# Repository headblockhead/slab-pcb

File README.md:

# Slab PCB

The full PCB, schematics, and gerber downloads for the [Slab keyboard project](https://github.com/headblockhead/slab).

Downloads are in the releases section.

## Layers

- The layer `User.3` stores non-polygon versions of the silkscreen text elements that can be edited.
- The layer `User.6` stores a printable outline of keyswitch locations, so a keymap can be drawn on paper to test the layout.

## Building

This project uses [Nix](https://nixos.org) for CI/CD only, to generate gerber files using KiCAD's CLI.

## Sponsorship

The PCB prototypes for this version of the Slab keyboard project were kindly provided by [PCBX](https://link.pcbx.com/fddd) for free!

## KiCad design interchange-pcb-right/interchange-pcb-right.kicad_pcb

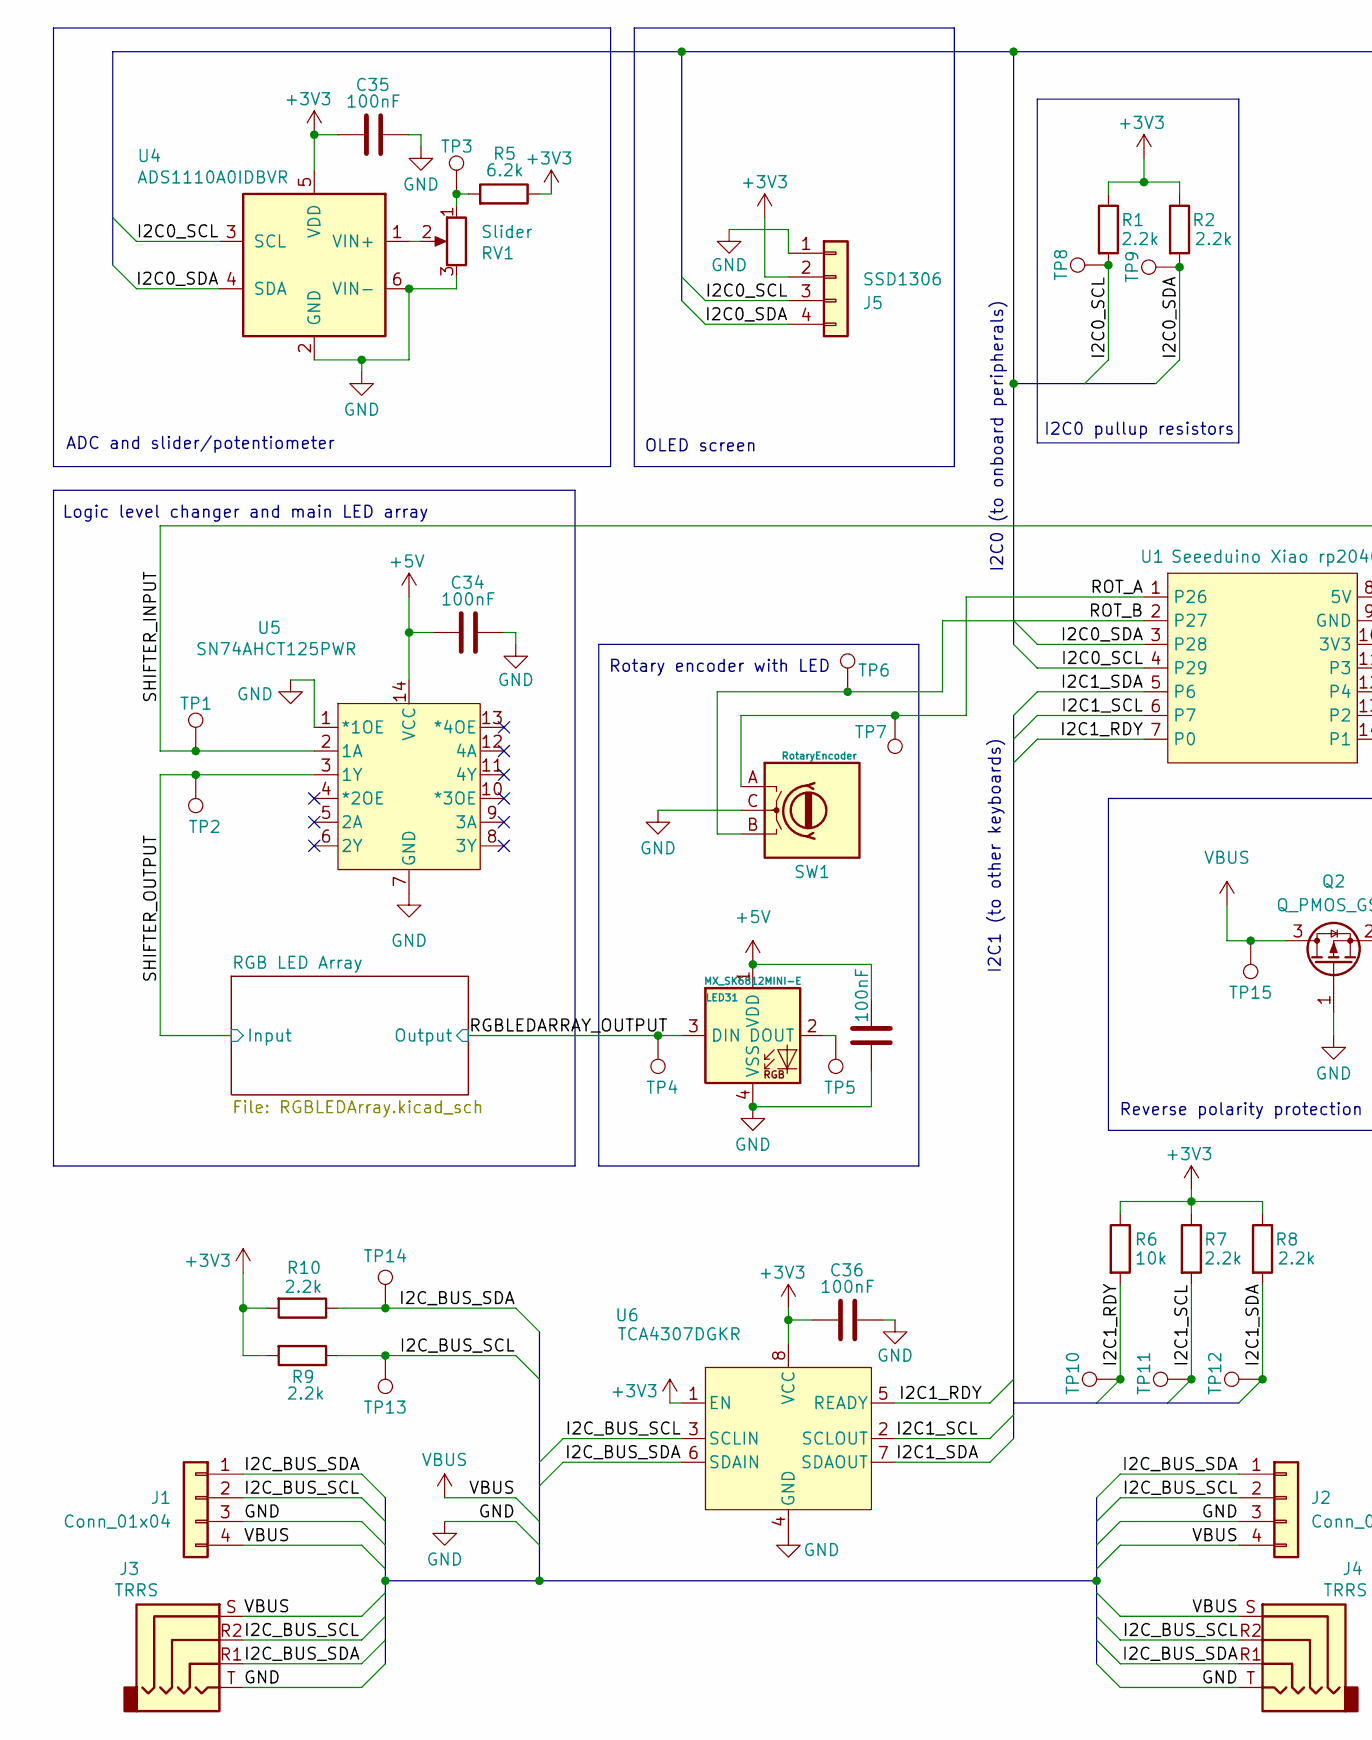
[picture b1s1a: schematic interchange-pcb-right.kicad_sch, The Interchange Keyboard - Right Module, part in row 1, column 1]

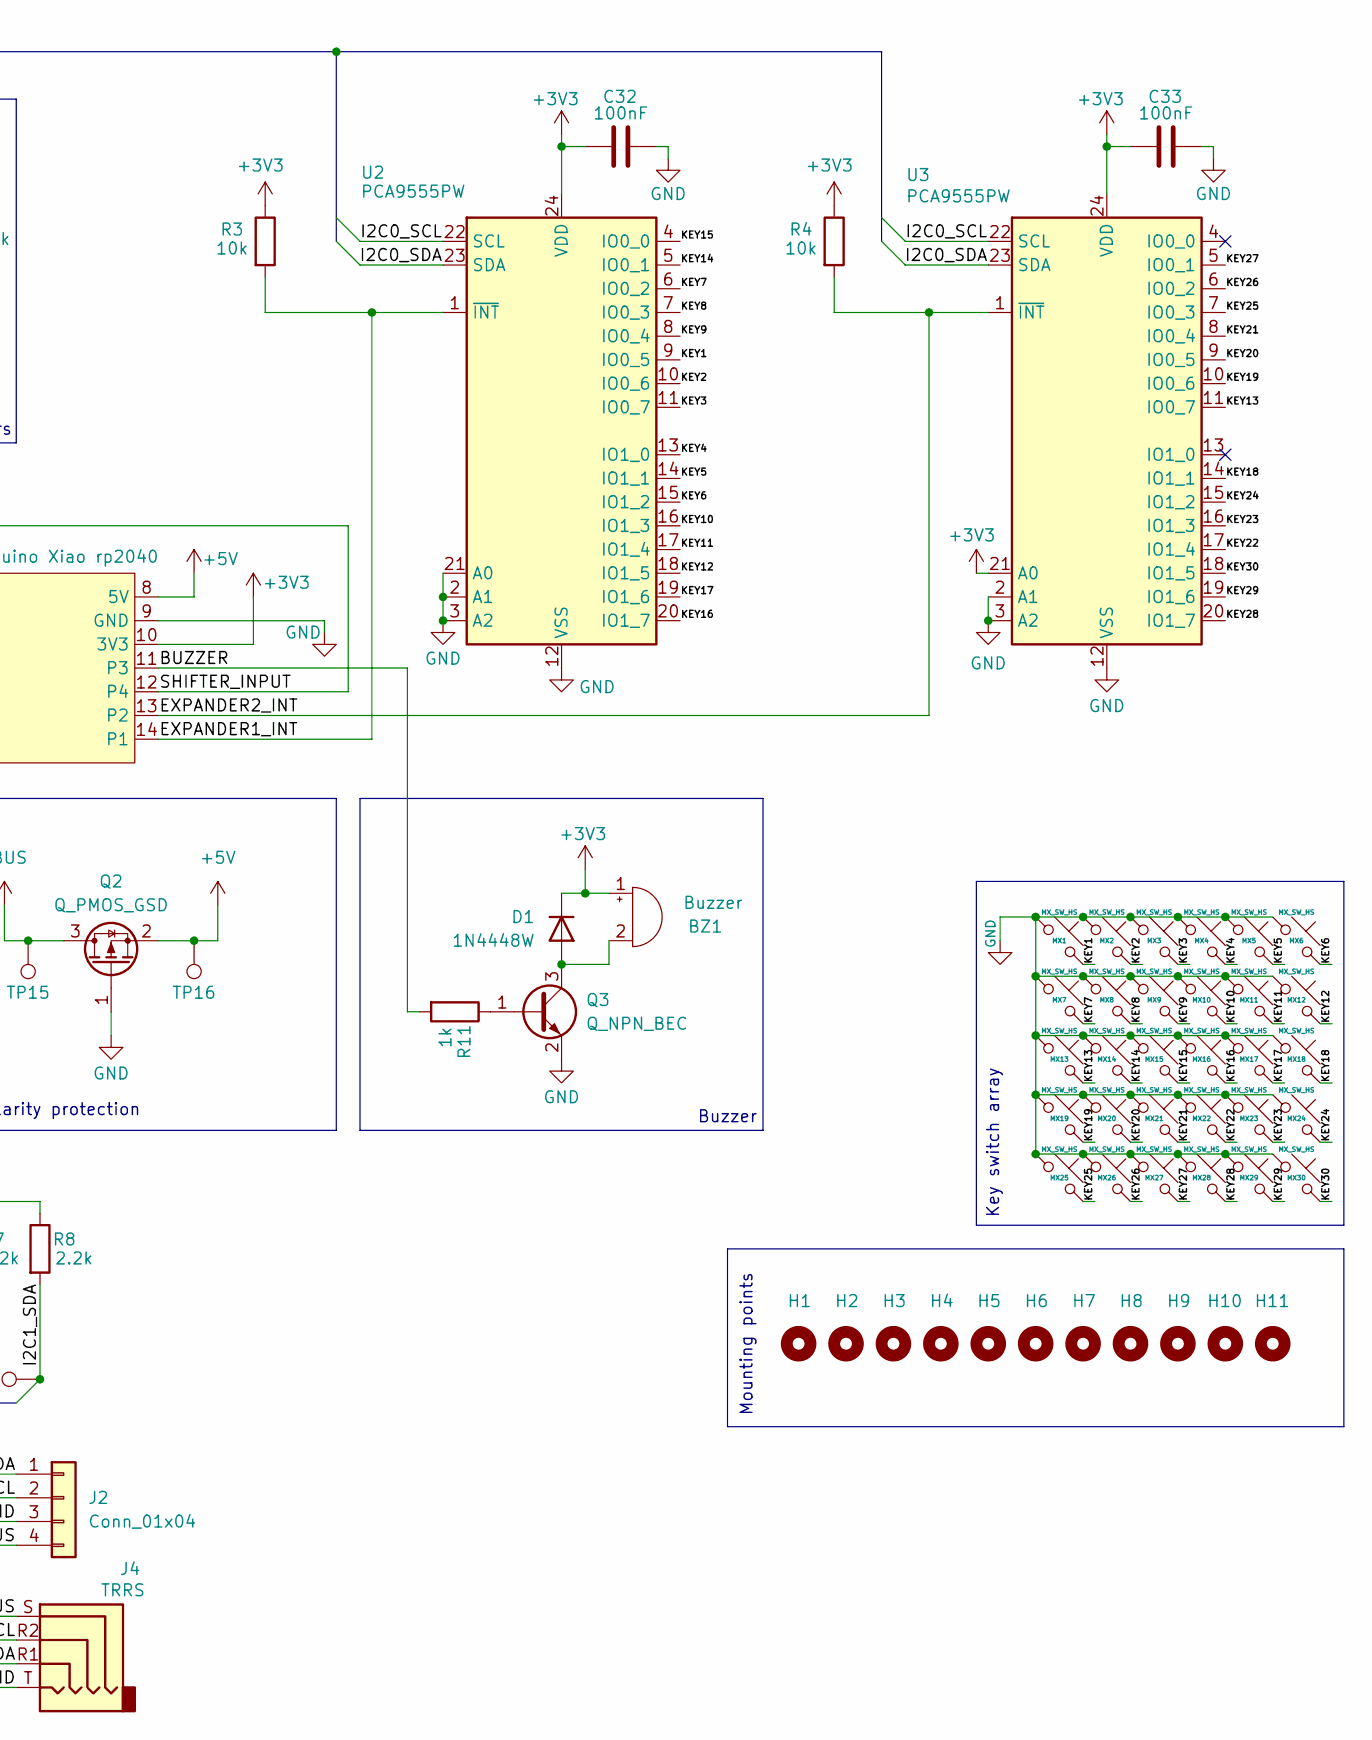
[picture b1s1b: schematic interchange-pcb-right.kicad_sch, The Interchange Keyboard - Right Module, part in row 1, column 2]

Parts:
BZ1: Buzzer; buzzer; LCSC C94599
C31, C32, C33, C34, C35, C36: 100nF; C_0603_1608Metric_Pad1.08x0.95mm_HandSolder; LCSC C14663
D1: 1N4448W; D_SOD-123; LCSC C5190208
H1, H2, H3, H4, H5, H6, H7, H8, H9, H10, H11: MountingHole_Pad; MountingHole_3.2mm_M3
J1: Conn_01x04; MagneticSlot_Right
J2: Conn_01x04; MagneticSlot_Left
J3, J4: TRRS; Jack_3.5mm_KoreanHropartsElec_PJ-320D-4A_Horizontal; LCSC C95562
J5: SSD1306; SSD1306_128x32; LCSC C5248081
LED31: MX_SK6812MINI-E; LED_6028R_Custom; LCSC C5149201
MX1, MX2, MX3, MX4, MX5, MX6, MX7, MX8, MX9, MX10, MX11, MX12, MX13, MX14, MX15, MX16, MX17, MX18, MX19, MX20, MX21, MX22, MX23, MX24, MX25, MX26, MX27, MX28, MX29, MX30: MX_SW_HS; SW_choc_mx_combined; LCSC C41430893
Q2: Q_PMOS_GSD; SOT-23_Handsoldering; LCSC C54157814
Q3: Q_NPN_BEC; SOT-23_Handsoldering; LCSC C57668
R1, R2, R7, R8, R9, R10: 2.2k; R_0603_1608Metric_Pad0.98x0.95mm_HandSolder; LCSC C4190
R3, R4, R6: 10k; R_0603_1608Metric_Pad0.98x0.95mm_HandSolder; LCSC C2930027
R5: 6.2k; R_0603_1608Metric_Pad0.98x0.95mm_HandSolder; LCSC C2907186
R11: 1k; R_0603_1608Metric_Pad0.98x0.95mm_HandSolder; LCSC C2907113
RV1: Slider; SW_RS45111A900F_ALPS; LCSC C470640
SW1: RotaryEncoder; RotaryEncoder_Alps_EC12E_Vertical_H20mm_Custom; LCSC C351235
TP1, TP2, TP3, TP4, TP5, TP6, TP7, TP8, TP9, TP10, TP11, TP12, TP13, TP14, TP15, TP16: TestPoint; TestPoint_Pad_D1.5mm
U1: Seeeduino Xiao rp2040; Xiao_rp2040_AC_Reflow_Custom
U2, U3: PCA9555PW; TSSOP-24_4.4x7.8mm_P0.65mm; LCSC C128392
U4: ADS1110A0IDBVR; SOT-23-6_Handsoldering; LCSC C16598
U5: SN74AHCT125PWR; LCSC C36365
U6: TCA4307DGKR; SOIC8_DGK_TEX; LCSC C880333

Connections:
+3V3: BZ1.1 (+), C32.2, C33.2, C35.2, C36.2, D1.1 (K), J5.2, R1.1, R2.1, R3.1, R4.1, R5.1, R6.1, R7.1, R8.1, R9.2, R10.2, U1.10 (3V3), U2.24 (VDD), U3.21 (A0), U3.24 (VDD), U4.5 (VDD), U6.1 (EN), U6.8 (VCC)
+5V: C31.2, C34.2, LED31.1 (VDD), Q2.2 (S), TP16.1 (1_1), U1.8 (5V), U5.14 (VCC); also elsewhere on the board
/BUZZER: R11.2, U1.11 (P3)
/EXPANDER1_INT: R3.2, U1.14 (P1), U2.1 (~INT)
/EXPANDER2_INT: R4.2, U1.13 (P2), U3.1 (~INT)
/I2C0_SCL: J5.3, R1.2, TP8.1 (1_1), U1.4 (P29), U2.22 (SCL), U3.22 (SCL), U4.3 (SCL)
/I2C0_SDA: J5.4, R2.2, TP9.1 (1_1), U1.3 (P28), U2.23 (SDA), U3.23 (SDA), U4.4 (SDA)
/I2C1_RDY: R6.2, TP10.1 (1_1), U1.7 (P0), U6.5 (READY)
/I2C1_SCL: R7.2, TP11.1 (1_1), U1.6 (P7), U6.2 (SCLOUT)
/I2C1_SDA: R8.2, TP12.1 (1_1), U1.5 (P6), U6.7 (SDAOUT)
/I2C_BUS_SCL: J1.2, J2.2, J3.R2, J4.R2, R9.1, TP13.1 (1_1), U6.3 (SCLIN)
/I2C_BUS_SDA: J1.1, J2.1, J3.R1, J4.R1, R10.1, TP14.1 (1_1), U6.6 (SDAIN)
/KEY1: MX1.2, U2.9 (IO0_5)
/KEY2: MX2.2, U2.10 (IO0_6)
/KEY3: MX3.2, U2.11 (IO0_7)
/KEY4: MX4.2, U2.13 (IO1_0)
/KEY5: MX5.2, U2.14 (IO1_1)
/KEY6: MX6.2, U2.15 (IO1_2)
/KEY7: MX7.2, U2.6 (IO0_2)
/KEY8: MX8.2, U2.7 (IO0_3)
/KEY9: MX9.2, U2.8 (IO0_4)
/KEY10: MX10.2, U2.16 (IO1_3)
/KEY11: MX11.2, U2.17 (IO1_4)
/KEY12: MX12.2, U2.18 (IO1_5)
/KEY13: MX13.2, U3.11 (IO0_7)
/KEY14: MX14.2, U2.5 (IO0_1)
/KEY15: MX15.2, U2.4 (IO0_0)
/KEY16: MX16.2, U2.20 (IO1_7)
/KEY17: MX17.2, U2.19 (IO1_6)
/KEY18: MX18.2, U3.14 (IO1_1)
/KEY19: MX19.2, U3.10 (IO0_6)
/KEY20: MX20.2, U3.9 (IO0_5)
/KEY21: MX21.2, U3.8 (IO0_4)
/KEY22: MX22.2, U3.17 (IO1_4)
/KEY23: MX23.2, U3.16 (IO1_3)
/KEY24: MX24.2, U3.15 (IO1_2)
/KEY25: MX25.2, U3.7 (IO0_3)
/KEY26: MX26.2, U3.6 (IO0_2)
/KEY27: MX27.2, U3.5 (IO0_1)
/KEY28: MX28.2, U3.20 (IO1_7)
/KEY29: MX29.2, U3.19 (IO1_6)
/KEY30: MX30.2, U3.18 (IO1_5)
/RGBLEDARRAY_OUTPUT: LED31.3 (DIN), TP4.1 (1_1); also elsewhere on the board
/ROT_A: SW1.A, TP7.1 (1_1), U1.1 (P26)
/ROT_B: SW1.B, TP6.1 (1_1), U1.2 (P27)
/SHIFTER_INPUT: TP1.1 (1_1), U1.12 (P4), U5.2 (1A)
/SHIFTER_OUTPUT: TP2.1 (1_1), U5.3 (1Y); also elsewhere on the board
GND: C31.1, C32.1, C33.1, C34.1, C35.1, C36.1, J1.3, J2.3, J3.T, J4.T, J5.1, LED31.4 (VSS), MX1.1, MX2.1, MX3.1, MX4.1, MX5.1, MX6.1, MX7.1, MX8.1, MX9.1, MX10.1, MX11.1, MX12.1, MX13.1, MX14.1, MX15.1, MX16.1, MX17.1, MX18.1, MX19.1, MX20.1, MX21.1, MX22.1, MX23.1, MX24.1, MX25.1, MX26.1, MX27.1, MX28.1, MX29.1, MX30.1, Q2.1 (G), Q3.2 (E), RV1.3, SW1.C, U1.9 (GND), U2.2 (A1), U2.3 (A2), U2.12 (VSS), U2.21 (A0), U3.2 (A1), U3.3 (A2), U3.12 (VSS), U4.2 (GND), U4.6 (VIN-), U5.1 (*1OE), U5.7 (GND), U6.4 (GND); also elsewhere on the board
unnamed: BZ1.2 (-), D1.2 (A), Q3.3 (C)
unnamed: LED31.2 (DOUT), TP5.1 (1_1)
unnamed: Q3.1 (B), R11.1
unnamed: R5.2, RV1.1, TP3.1 (1_1)
unnamed: RV1.2, U4.1 (VIN+)
VBUS: J1.4, J2.4, J3.S, J4.S, Q2.3 (D), TP15.1 (1_1)

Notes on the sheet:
I2C0 (to onboard peripherals)
I2C1 (to other keyboards)
Mounting points
OLED screen
Reverse polarity protection
Rotary encoder with LED
Buzzer
I2C0 pullup resistors
ADC and slider/potentiometer
Key switch array
Logic level changer and main LED array

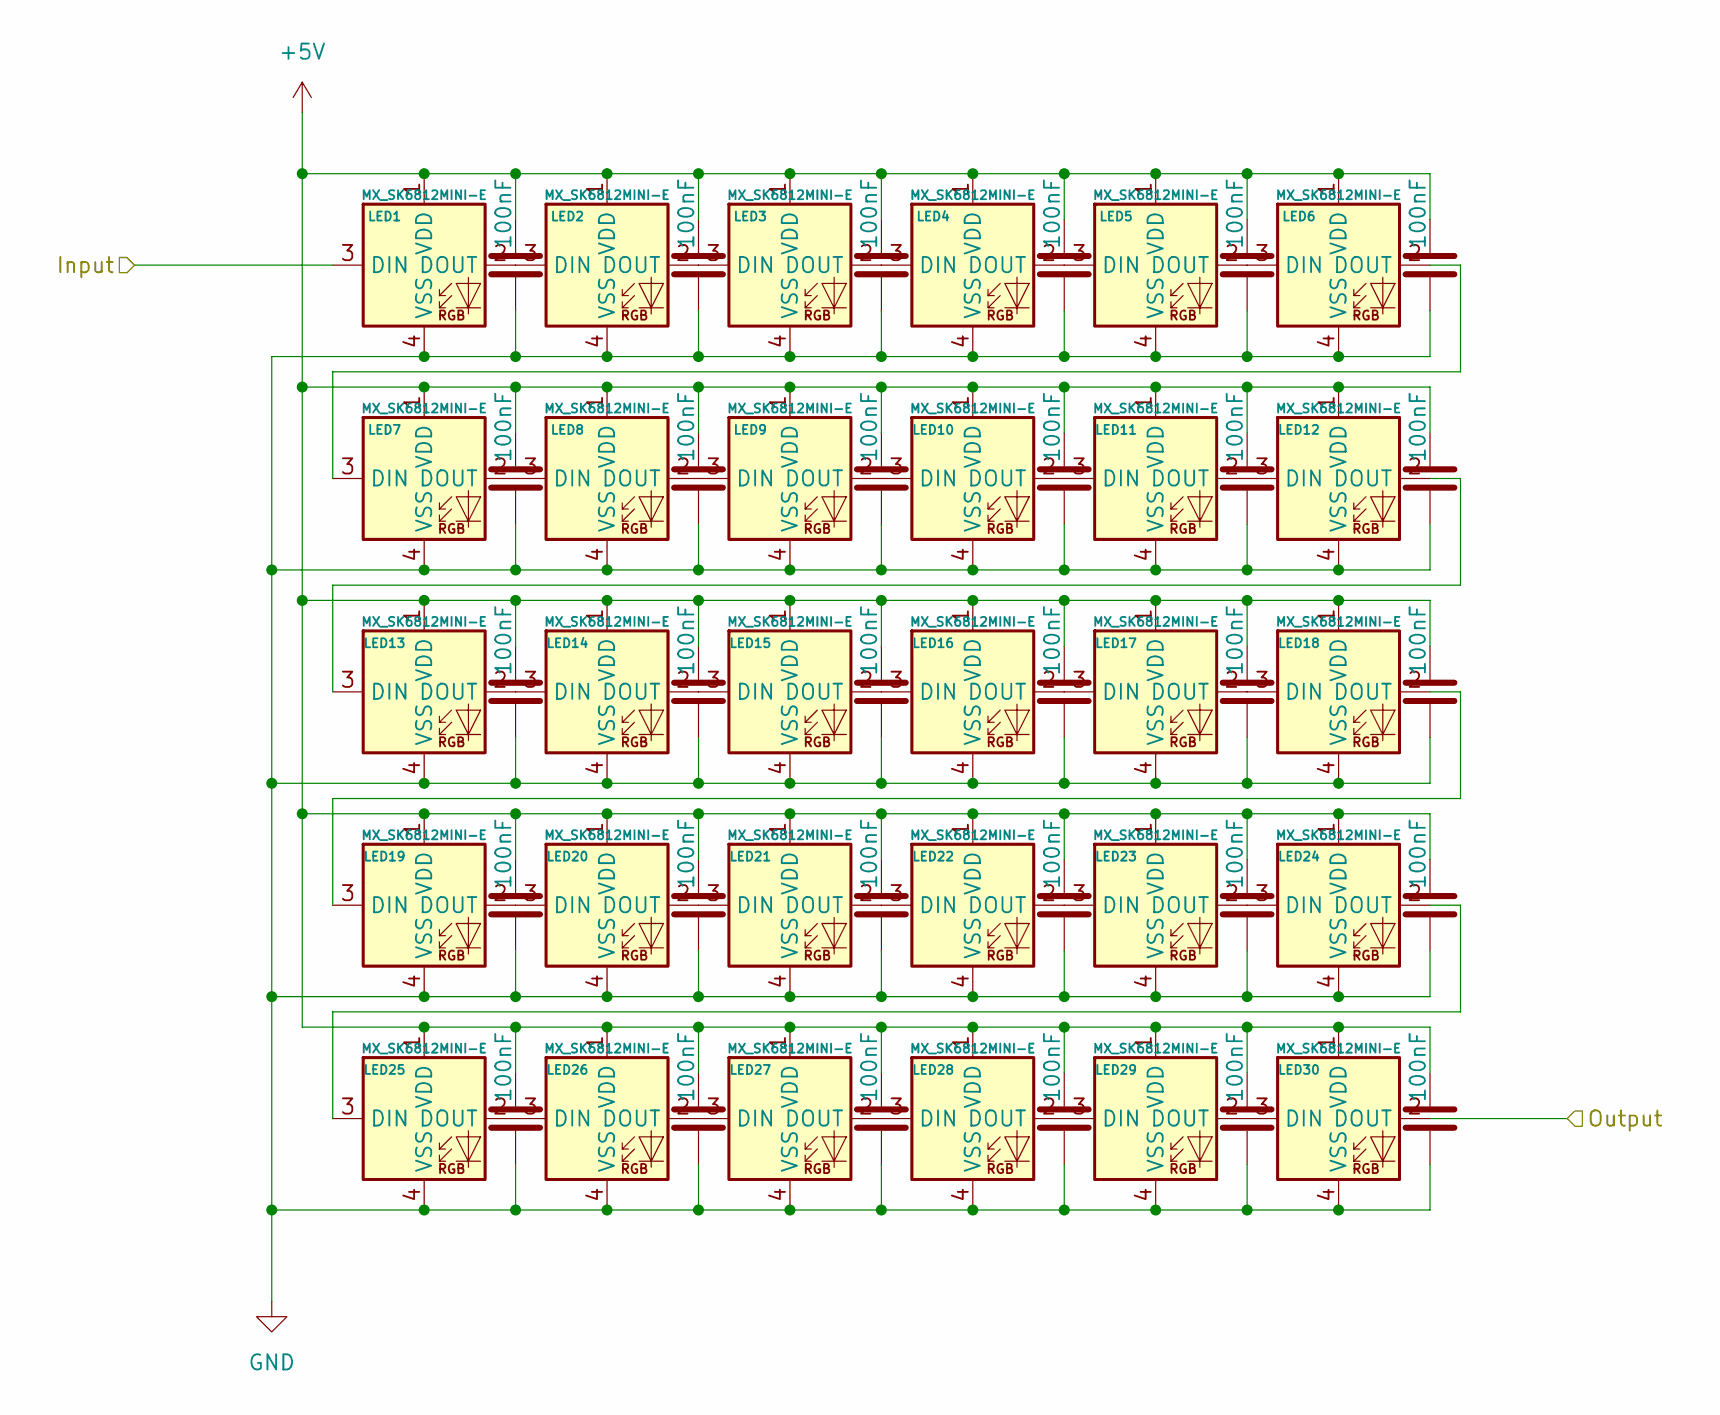
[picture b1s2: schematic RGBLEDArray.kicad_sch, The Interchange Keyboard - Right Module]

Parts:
C1, C2, C3, C4, C5, C6, C7, C8, C9, C10, C11, C12, C13, C14, C15, C16, C17, C18, C19, C20, C21, C22, C23, C24, C25, C26, C27, C28, C29, C30: 100nF; C_0603_1608Metric_Pad1.08x0.95mm_HandSolder; LCSC C14663
LED1, LED2, LED3, LED4, LED5, LED6, LED7, LED8, LED9, LED10, LED11, LED12, LED13, LED14, LED15, LED16, LED17, LED18, LED19, LED20, LED21, LED22, LED23, LED24, LED25, LED26, LED27, LED28, LED29, LED30: MX_SK6812MINI-E; LED_MX_6028R-ROT_Custom; LCSC C5149201

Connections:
+5V: C1.2, C2.2, C3.2, C4.2, C5.2, C6.2, C7.2, C8.2, C9.2, C10.2, C11.2, C12.2, C13.2, C14.2, C15.2, C16.2, C17.2, C18.2, C19.2, C20.2, C21.2, C22.2, C23.2, C24.2, C25.2, C26.2, C27.2, C28.2, C29.2, C30.2, LED1.1 (VDD), LED2.1 (VDD), LED3.1 (VDD), LED4.1 (VDD), LED5.1 (VDD), LED6.1 (VDD), LED7.1 (VDD), LED8.1 (VDD), LED9.1 (VDD), LED10.1 (VDD), LED11.1 (VDD), LED12.1 (VDD), LED13.1 (VDD), LED14.1 (VDD), LED15.1 (VDD), LED16.1 (VDD), LED17.1 (VDD), LED18.1 (VDD), LED19.1 (VDD), LED20.1 (VDD), LED21.1 (VDD), LED22.1 (VDD), LED23.1 (VDD), LED24.1 (VDD), LED25.1 (VDD), LED26.1 (VDD), LED27.1 (VDD), LED28.1 (VDD), LED29.1 (VDD), LED30.1 (VDD); also elsewhere on the board
/RGBLEDARRAY_OUTPUT: LED30.2 (DOUT); also elsewhere on the board
/SHIFTER_OUTPUT: LED1.3 (DIN); also elsewhere on the board
GND: C1.1, C2.1, C3.1, C4.1, C5.1, C6.1, C7.1, C8.1, C9.1, C10.1, C11.1, C12.1, C13.1, C14.1, C15.1, C16.1, C17.1, C18.1, C19.1, C20.1, C21.1, C22.1, C23.1, C24.1, C25.1, C26.1, C27.1, C28.1, C29.1, C30.1, LED1.4 (VSS), LED2.4 (VSS), LED3.4 (VSS), LED4.4 (VSS), LED5.4 (VSS), LED6.4 (VSS), LED7.4 (VSS), LED8.4 (VSS), LED9.4 (VSS), LED10.4 (VSS), LED11.4 (VSS), LED12.4 (VSS), LED13.4 (VSS), LED14.4 (VSS), LED15.4 (VSS), LED16.4 (VSS), LED17.4 (VSS), LED18.4 (VSS), LED19.4 (VSS), LED20.4 (VSS), LED21.4 (VSS), LED22.4 (VSS), LED23.4 (VSS), LED24.4 (VSS), LED25.4 (VSS), LED26.4 (VSS), LED27.4 (VSS), LED28.4 (VSS), LED29.4 (VSS), LED30.4 (VSS); also elsewhere on the board
unnamed: LED1.2 (DOUT), LED2.3 (DIN)
unnamed: LED2.2 (DOUT), LED3.3 (DIN)
unnamed: LED3.2 (DOUT), LED4.3 (DIN)
unnamed: LED4.2 (DOUT), LED5.3 (DIN)
unnamed: LED5.2 (DOUT), LED6.3 (DIN)
unnamed: LED6.2 (DOUT), LED7.3 (DIN)
unnamed: LED7.2 (DOUT), LED8.3 (DIN)
unnamed: LED8.2 (DOUT), LED9.3 (DIN)
unnamed: LED9.2 (DOUT), LED10.3 (DIN)
unnamed: LED10.2 (DOUT), LED11.3 (DIN)
unnamed: LED11.2 (DOUT), LED12.3 (DIN)
unnamed: LED12.2 (DOUT), LED13.3 (DIN)
unnamed: LED13.2 (DOUT), LED14.3 (DIN)
unnamed: LED14.2 (DOUT), LED15.3 (DIN)
unnamed: LED15.2 (DOUT), LED16.3 (DIN)
unnamed: LED16.2 (DOUT), LED17.3 (DIN)
unnamed: LED17.2 (DOUT), LED18.3 (DIN)
unnamed: LED18.2 (DOUT), LED19.3 (DIN)
unnamed: LED19.2 (DOUT), LED20.3 (DIN)
unnamed: LED20.2 (DOUT), LED21.3 (DIN)
unnamed: LED21.2 (DOUT), LED22.3 (DIN)
unnamed: LED22.2 (DOUT), LED23.3 (DIN)
unnamed: LED23.2 (DOUT), LED24.3 (DIN)
unnamed: LED24.2 (DOUT), LED25.3 (DIN)
unnamed: LED25.2 (DOUT), LED26.3 (DIN)
unnamed: LED26.2 (DOUT), LED27.3 (DIN)
unnamed: LED27.2 (DOUT), LED28.3 (DIN)
unnamed: LED28.2 (DOUT), LED29.3 (DIN)
unnamed: LED29.2 (DOUT), LED30.3 (DIN)

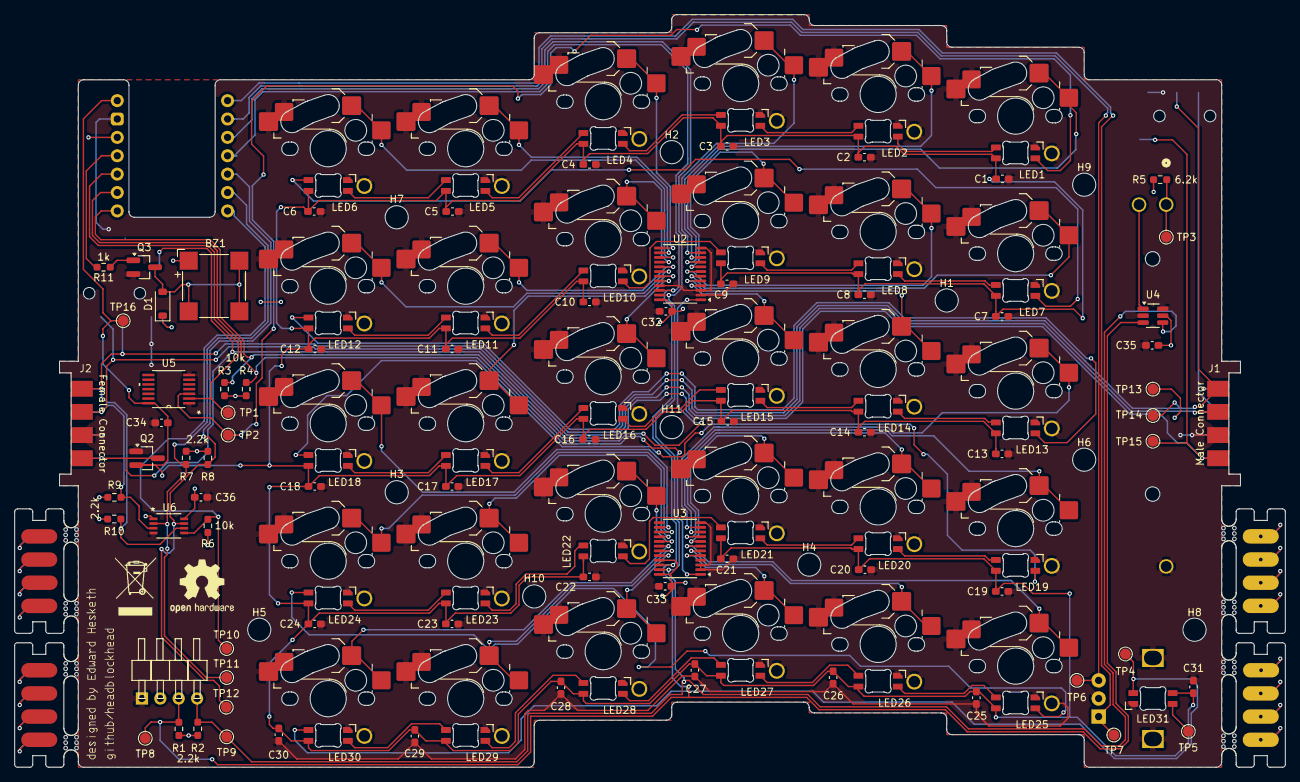
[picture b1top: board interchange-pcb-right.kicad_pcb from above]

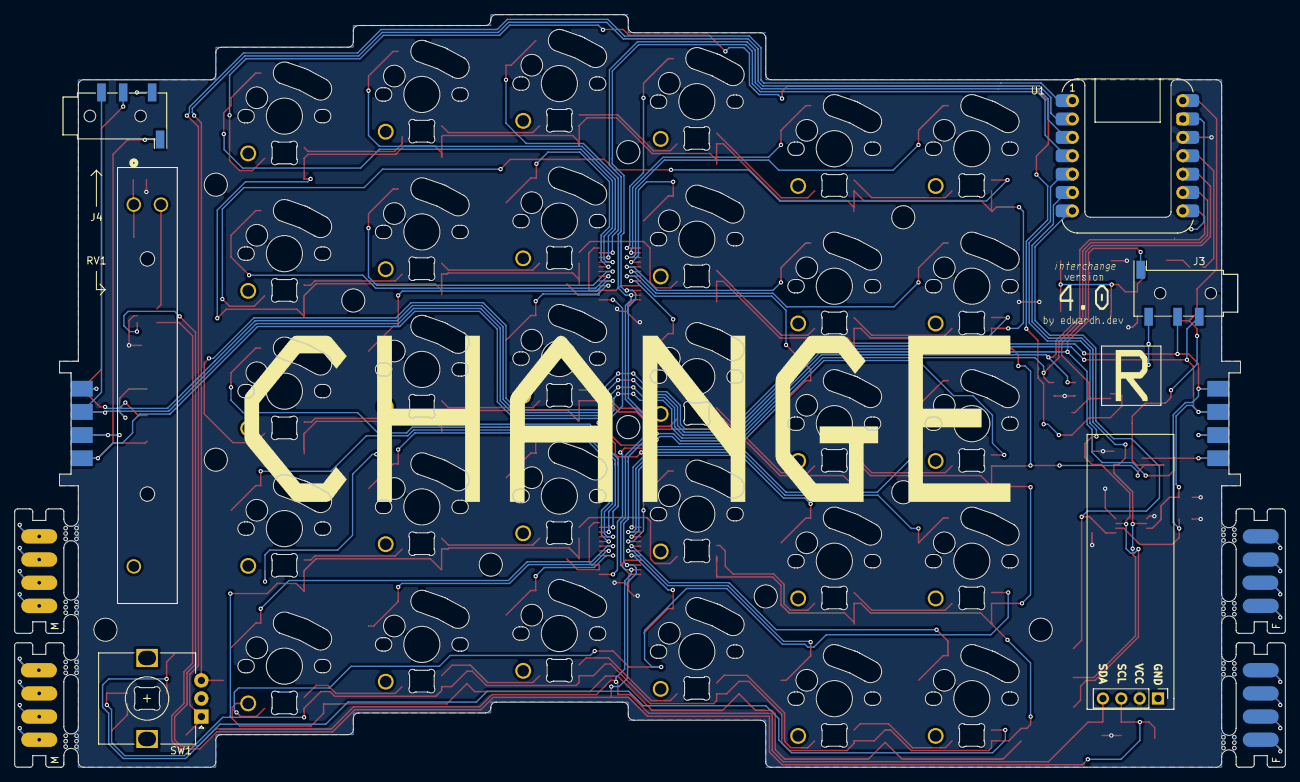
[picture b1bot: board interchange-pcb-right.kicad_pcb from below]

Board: 2 copper layers, 175.6 x 104.0 mm, 162 parts (6 on the bottom side), 83 nets.

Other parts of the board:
OSHW: OSHW-Logo2_9.8x8mm_SilkScreen
WEEE: WEEE-Logo_5.6x8mm_SilkScreen
mouse-bite-2mm-slot, mouse-bite-2mm-slot#2, mouse-bite-2mm-slot#3, mouse-bite-2mm-slot#4, mouse-bite-2mm-slot#5, mouse-bite-2mm-slot#6, mouse-bite-2mm-slot#7, mouse-bite-2mm-slot#8: VAL**; mouse-bite-2mm-slot

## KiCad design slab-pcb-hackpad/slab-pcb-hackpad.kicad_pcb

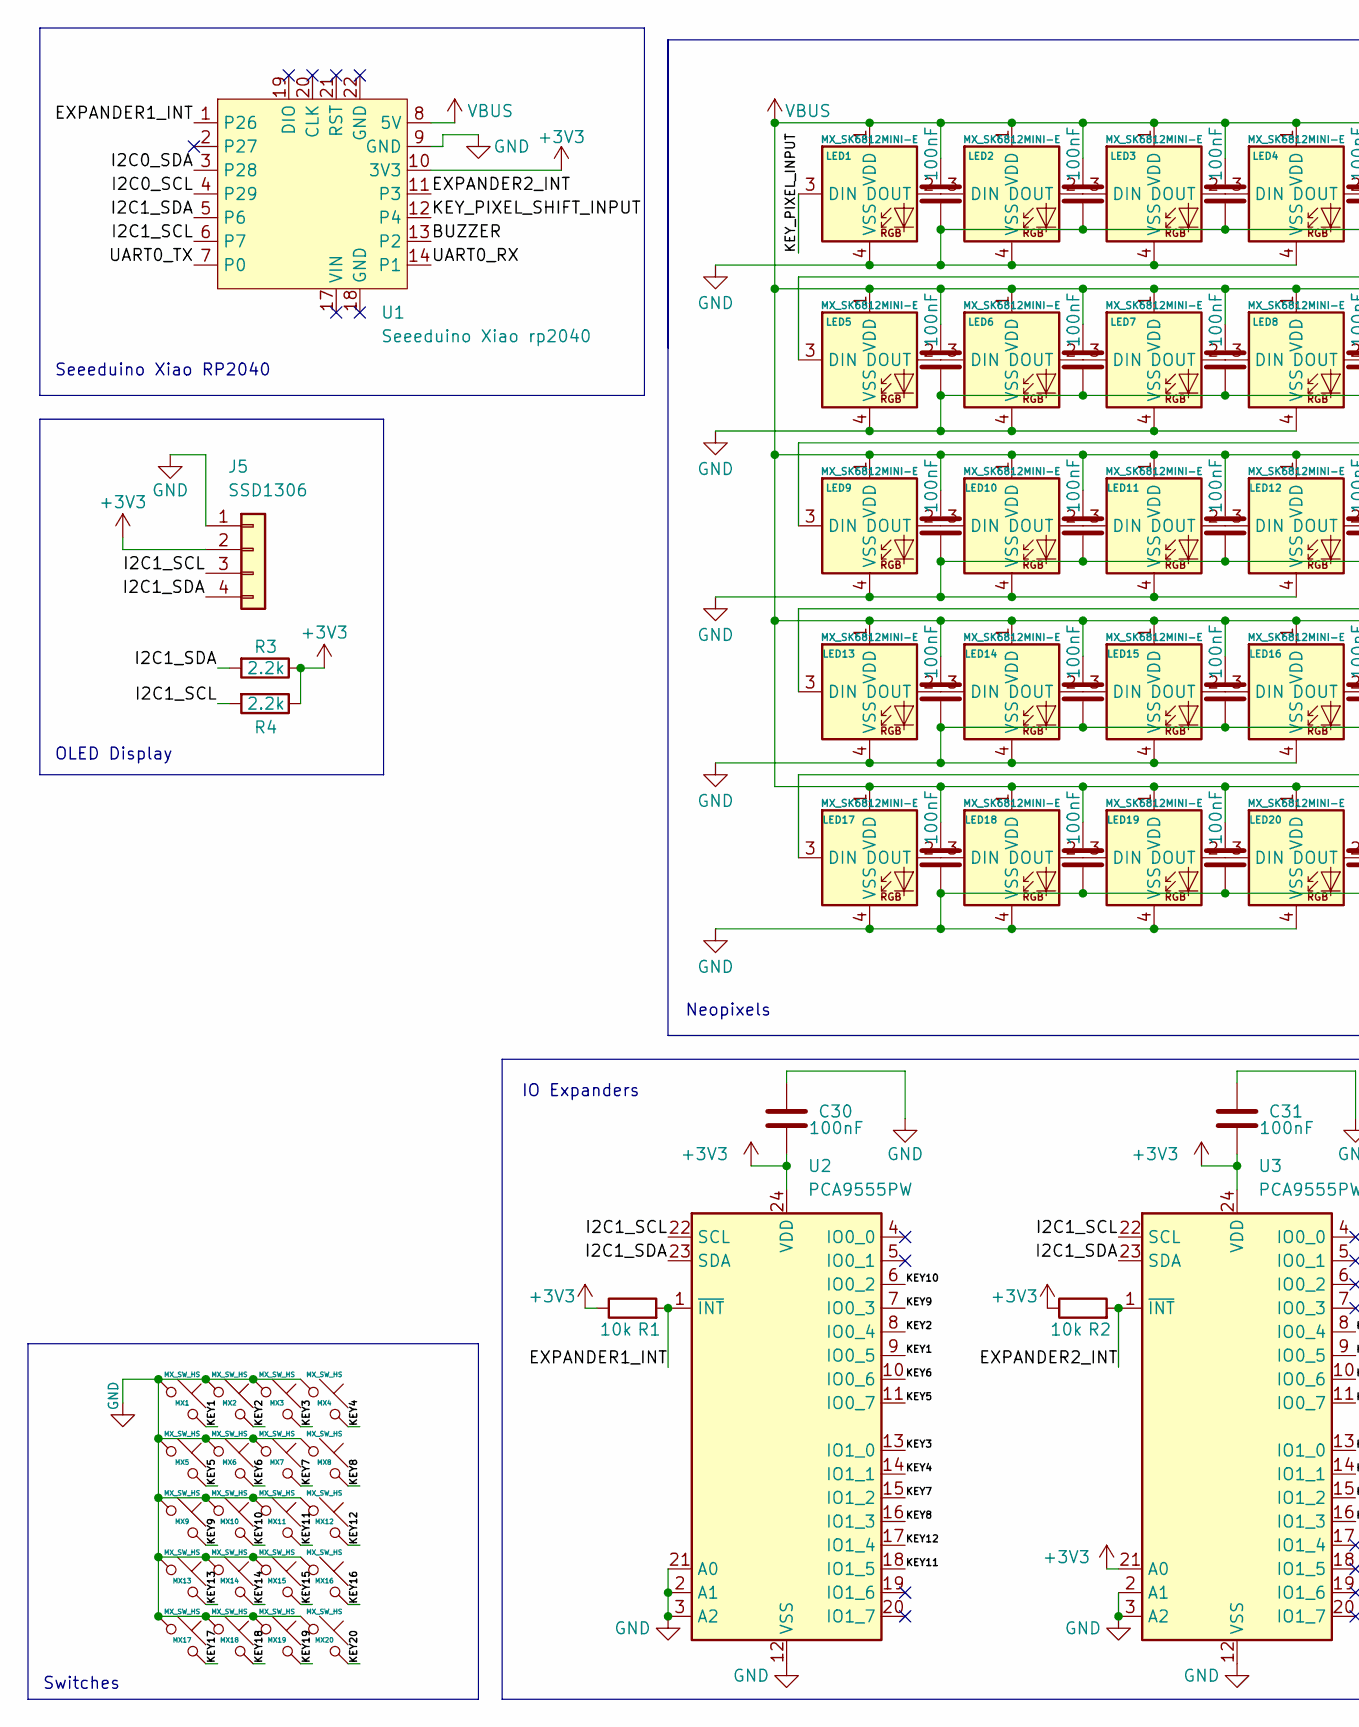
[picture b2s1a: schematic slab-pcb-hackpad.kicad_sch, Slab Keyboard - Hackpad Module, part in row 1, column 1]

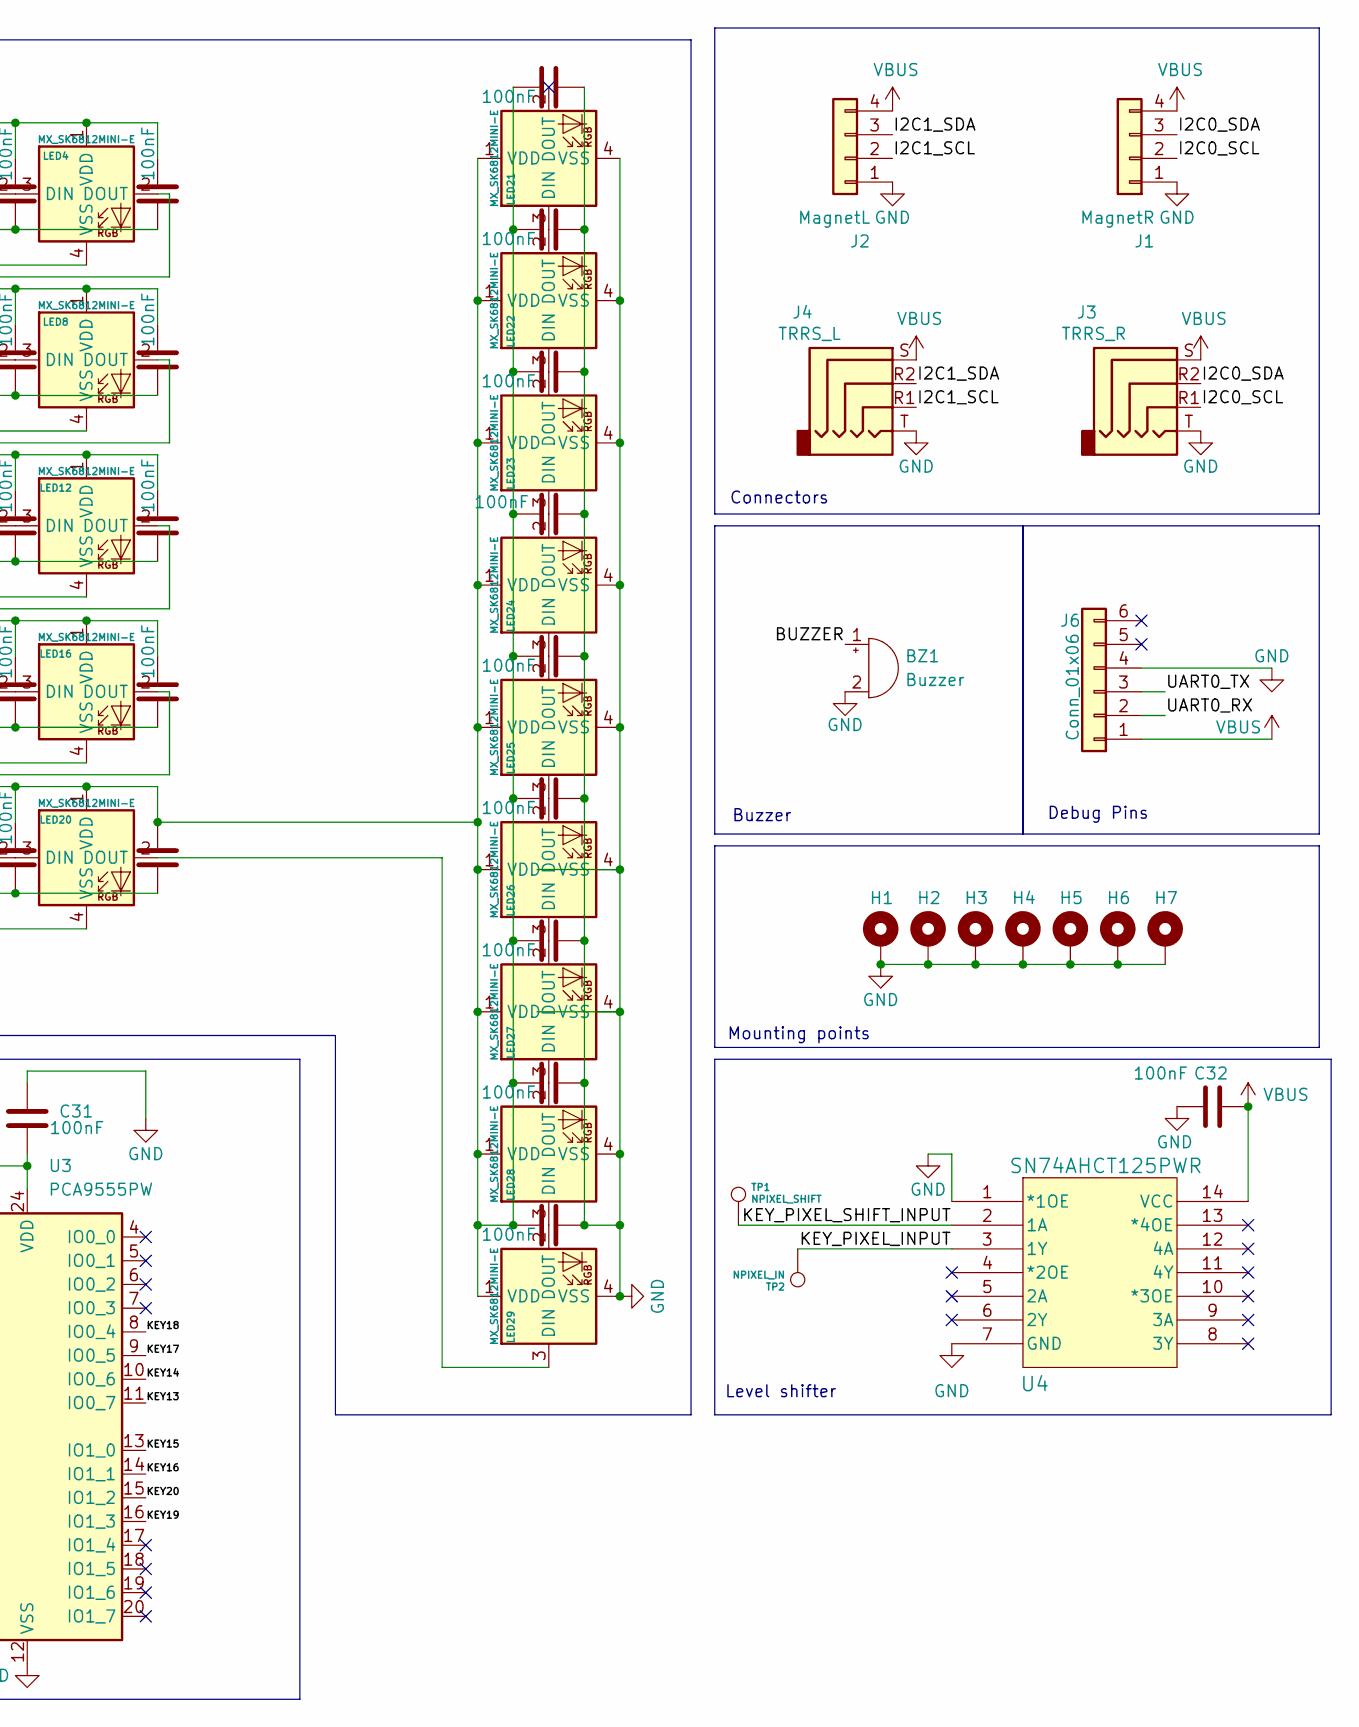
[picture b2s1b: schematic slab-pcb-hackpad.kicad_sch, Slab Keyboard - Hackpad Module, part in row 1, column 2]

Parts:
BZ1: Buzzer; buzzer
C1, C2, C3, C4, C5, C6, C7, C8, C9, C10, C11, C12, C13, C14, C15, C16, C17, C18, C19, C20, C21, C22, C23, C24, C25, C26, C27, C28, C29, C30, C31, C32: 100nF; C_0603_1608Metric_Pad1.08x0.95mm_HandSolder
H1, H2, H3, H4, H5, H6, H7: MountingHole_Pad; MountingHole_3.2mm_M3_Pad_TopBottom
J1: MagnetR; 5358_mag_connector_1x4_pads
J2: MagnetL; 5358_mag_connector_1x4_pins
J3: TRRS_R; Jack_3.5mm_KoreanHropartsElec_PJ-320D-4A_Horizontal
J4: TRRS_L; Jack_3.5mm_KoreanHropartsElec_PJ-320D-4A_Horizontal
J5: SSD1306; SSD1306_128x32
J6: Conn_01x06; PinHeader_1x06_P2.54mm_Vertical
LED1, LED2, LED3, LED4, LED5, LED6, LED7, LED8, LED9, LED10, LED11, LED12, LED13, LED14, LED15, LED16, LED17, LED18, LED19, LED20: MX_SK6812MINI-E; LED_MX_6028R-ROT_Custom
LED21, LED22, LED23, LED24, LED25, LED26, LED27, LED28, LED29: MX_SK6812MINI-E; LED_6028R_Custom
MX1, MX2, MX3, MX4, MX5, MX6, MX7, MX8, MX9, MX10, MX11, MX12, MX13, MX14, MX15, MX16, MX17, MX18, MX19, MX20: MX_SW_HS; SW_choc_mx_combined
R1, R2: 10k; R_0603_1608Metric_Pad0.98x0.95mm_HandSolder
R3, R4: 2.2k; R_0603_1608Metric_Pad0.98x0.95mm_HandSolder
TP1: NPIXEL_SHIFT; TestPoint_Pad_1.0x1.0mm
TP2: NPIXEL_IN; TestPoint_Pad_1.0x1.0mm
U1: Seeeduino Xiao rp2040; Xiao_rp2040_AC_Reflow_Custom
U2, U3: PCA9555PW; TSSOP-24_4.4x7.8mm_P0.65mm
U4: SN74AHCT125PWR

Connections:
+3V3: C30.1, C31.1, J5.2, R1.1, R2.1, R3.1, R4.1, U1.10 (3V3), U2.24 (VDD), U3.21 (A0), U3.24 (VDD)
/BUZZER: BZ1.1 (+), U1.13 (P2)
/EXPANDER1_INT: R1.2, U1.1 (P26), U2.1 (~INT)
/EXPANDER2_INT: R2.2, U1.11 (P3), U3.1 (~INT)
/I2C0_SCL: J1.2, J3.R1, U1.4 (P29)
/I2C0_SDA: J1.3, J3.R2, U1.3 (P28)
/I2C1_SCL: J2.2, J4.R1, J5.3, R4.2, U1.6 (P7), U2.22 (SCL), U3.22 (SCL)
/I2C1_SDA: J2.3, J4.R2, J5.4, R3.2, U1.5 (P6), U2.23 (SDA), U3.23 (SDA)
/KEY1: MX1.2, U2.9 (IO0_5)
/KEY2: MX2.2, U2.8 (IO0_4)
/KEY3: MX3.2, U2.13 (IO1_0)
/KEY4: MX4.2, U2.14 (IO1_1)
/KEY5: MX5.2, U2.11 (IO0_7)
/KEY6: MX6.2, U2.10 (IO0_6)
/KEY7: MX7.2, U2.15 (IO1_2)
/KEY8: MX8.2, U2.16 (IO1_3)
/KEY9: MX9.2, U2.7 (IO0_3)
/KEY10: MX10.2, U2.6 (IO0_2)
/KEY11: MX11.2, U2.18 (IO1_5)
/KEY12: MX12.2, U2.17 (IO1_4)
/KEY13: MX13.2, U3.11 (IO0_7)
/KEY14: MX14.2, U3.10 (IO0_6)
/KEY15: MX15.2, U3.13 (IO1_0)
/KEY16: MX16.2, U3.14 (IO1_1)
/KEY17: MX17.2, U3.9 (IO0_5)
/KEY18: MX18.2, U3.8 (IO0_4)
/KEY19: MX19.2, U3.16 (IO1_3)
/KEY20: MX20.2, U3.15 (IO1_2)
/KEY_PIXEL_INPUT: LED1.3 (DIN), TP2.1, U4.3 (1Y)
/KEY_PIXEL_SHIFT_INPUT: TP1.1, U1.12 (P4), U4.2 (1A)
/UART0_RX: J6.2, U1.14 (P1)
/UART0_TX: J6.3, U1.7 (P0)
GND: BZ1.2 (-), C1.1, C2.1, C3.1, C4.1, C5.1, C6.1, C7.1, C8.1, C9.1, C10.1, C11.1, C12.1, C13.1, C14.1, C15.1, C16.1, C17.1, C18.1, C19.1, C20.1, C21.1, C22.1, C23.1, C24.1, C25.1, C26.1, C27.1, C28.1, C29.1, C30.2, C31.2, C32.1, H1.1, H2.1, H3.1, H4.1, H5.1, H6.1, H7.1, J1.1, J2.1, J3.T, J4.T, J5.1, J6.4, LED1.4 (VSS), LED2.4 (VSS), LED3.4 (VSS), LED4.4 (VSS), LED5.4 (VSS), LED6.4 (VSS), LED7.4 (VSS), LED8.4 (VSS), LED9.4 (VSS), LED10.4 (VSS), LED11.4 (VSS), LED12.4 (VSS), LED13.4 (VSS), LED14.4 (VSS), LED15.4 (VSS), LED16.4 (VSS), LED17.4 (VSS), LED18.4 (VSS), LED19.4 (VSS), LED20.4 (VSS), LED21.4 (VSS), LED22.4 (VSS), LED23.4 (VSS), LED24.4 (VSS), LED25.4 (VSS), LED26.4 (VSS), LED27.4 (VSS), LED28.4 (VSS), LED29.4 (VSS), MX1.1, MX2.1, MX3.1, MX4.1, MX5.1, MX6.1, MX7.1, MX8.1, MX9.1, MX10.1, MX11.1, MX12.1, MX13.1, MX14.1, MX15.1, MX16.1, MX17.1, MX18.1, MX19.1, MX20.1, U1.9 (GND), U2.2 (A1), U2.3 (A2), U2.12 (VSS), U2.21 (A0), U3.2 (A1), U3.3 (A2), U3.12 (VSS), U4.1 (*1OE), U4.7 (GND)
unnamed: LED1.2 (DOUT), LED2.3 (DIN)
unnamed: LED2.2 (DOUT), LED3.3 (DIN)
unnamed: LED3.2 (DOUT), LED4.3 (DIN)
unnamed: LED4.2 (DOUT), LED5.3 (DIN)
unnamed: LED5.2 (DOUT), LED6.3 (DIN)
unnamed: LED6.2 (DOUT), LED7.3 (DIN)
unnamed: LED7.2 (DOUT), LED8.3 (DIN)
unnamed: LED8.2 (DOUT), LED9.3 (DIN)
unnamed: LED9.2 (DOUT), LED10.3 (DIN)
unnamed: LED10.2 (DOUT), LED11.3 (DIN)
unnamed: LED11.2 (DOUT), LED12.3 (DIN)
unnamed: LED12.2 (DOUT), LED13.3 (DIN)
unnamed: LED13.2 (DOUT), LED14.3 (DIN)
unnamed: LED14.2 (DOUT), LED15.3 (DIN)
unnamed: LED15.2 (DOUT), LED16.3 (DIN)
unnamed: LED16.2 (DOUT), LED17.3 (DIN)
unnamed: LED17.2 (DOUT), LED18.3 (DIN)
unnamed: LED18.2 (DOUT), LED19.3 (DIN)
unnamed: LED19.2 (DOUT), LED20.3 (DIN)
unnamed: LED20.2 (DOUT), LED29.3 (DIN)
unnamed: LED21.3 (DIN), LED22.2 (DOUT)
unnamed: LED22.3 (DIN), LED23.2 (DOUT)
unnamed: LED23.3 (DIN), LED24.2 (DOUT)
unnamed: LED24.3 (DIN), LED25.2 (DOUT)
unnamed: LED25.3 (DIN), LED26.2 (DOUT)
unnamed: LED26.3 (DIN), LED27.2 (DOUT)
unnamed: LED27.3 (DIN), LED28.2 (DOUT)
unnamed: LED28.3 (DIN), LED29.2 (DOUT)
VBUS: C1.2, C2.2, C3.2, C4.2, C5.2, C6.2, C7.2, C8.2, C9.2, C10.2, C11.2, C12.2, C13.2, C14.2, C15.2, C16.2, C17.2, C18.2, C19.2, C20.2, C21.2, C22.2, C23.2, C24.2, C25.2, C26.2, C27.2, C28.2, C29.2, C32.2, J1.4, J2.4, J3.S, J4.S, J6.1, LED1.1 (VDD), LED2.1 (VDD), LED3.1 (VDD), LED4.1 (VDD), LED5.1 (VDD), LED6.1 (VDD), LED7.1 (VDD), LED8.1 (VDD), LED9.1 (VDD), LED10.1 (VDD), LED11.1 (VDD), LED12.1 (VDD), LED13.1 (VDD), LED14.1 (VDD), LED15.1 (VDD), LED16.1 (VDD), LED17.1 (VDD), LED18.1 (VDD), LED19.1 (VDD), LED20.1 (VDD), LED21.1 (VDD), LED22.1 (VDD), LED23.1 (VDD), LED24.1 (VDD), LED25.1 (VDD), LED26.1 (VDD), LED27.1 (VDD), LED28.1 (VDD), LED29.1 (VDD), U1.8 (5V), U4.14 (VCC)

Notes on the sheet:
Mounting points
Buzzer
Level shifter
Debug Pins
Connectors
Switches
Seeeduino Xiao RP2040
OLED Display
IO Expanders
Neopixels
